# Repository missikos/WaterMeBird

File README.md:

# WaterMeBird

##Video Instructions
https://www.youtube.com/playlist?list=PLXV-vJmVgkyYVAK37a0ae-BBcncbxYWD5

#Advanced:

##PCB:
TBA

##Programming:
TBA

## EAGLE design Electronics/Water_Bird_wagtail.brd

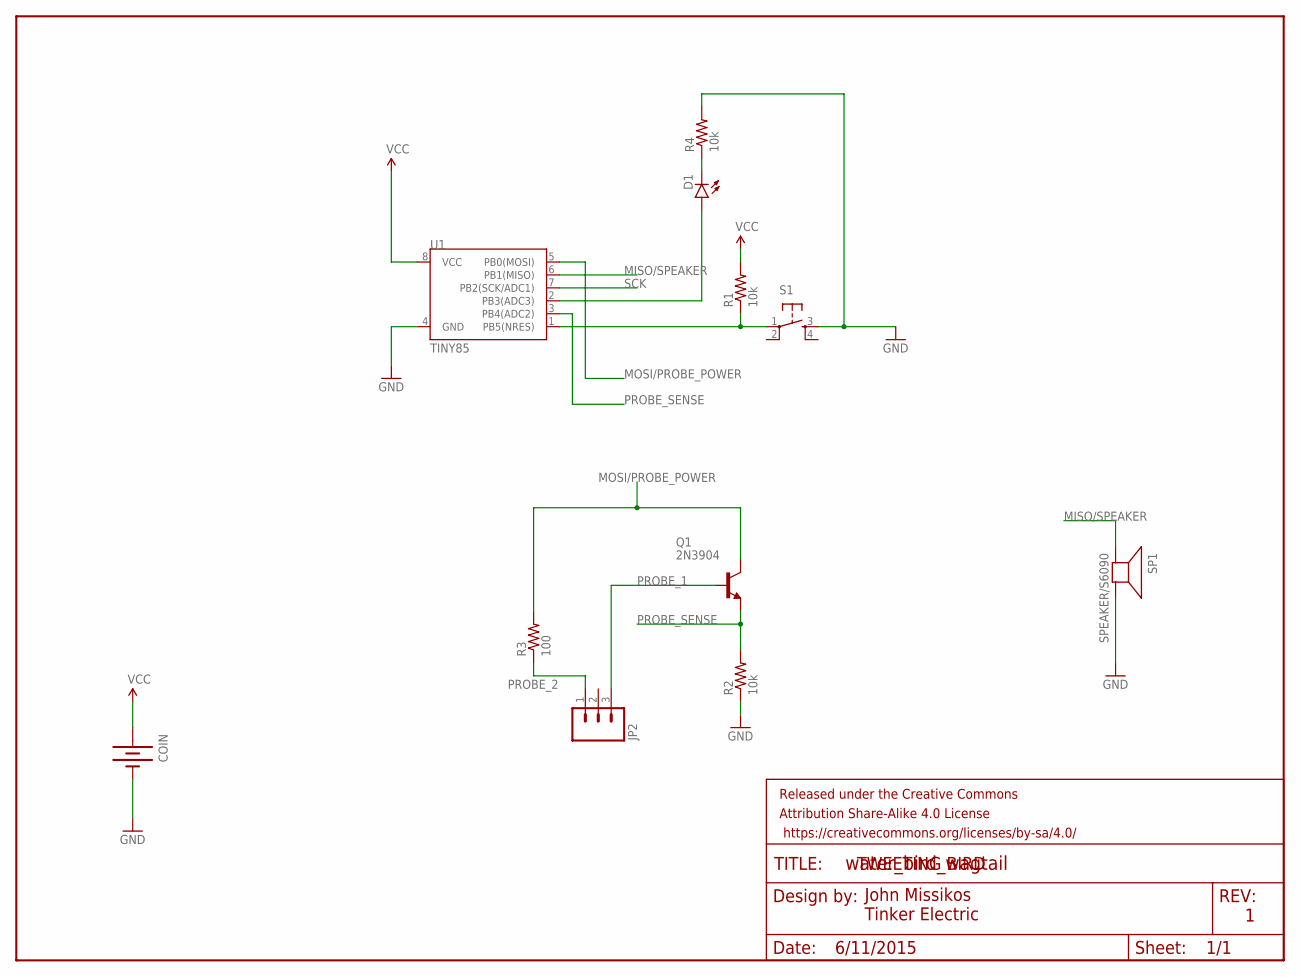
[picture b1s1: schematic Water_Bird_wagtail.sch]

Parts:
COIN: BATTERY_20MM20PTH; BATTCOM_20MM_PTH
D1: LED5MM
FRAME1: FRAME-LETTERNO_PACKAGE; DUMMY
JP2: M03-SCREW-5MM; SCREWTERMINAL-5MM-3
Q1: 2N3904; TO92-EBC-OVAL
R1, R2, R4: 10k; AXIAL-0.3
R3: 100; AXIAL-0.3
S1: TAC_SWITCHPTH; TACTILE-PTH
SP1: SPEAKER/S6090; S6090
U1: TINY85; DIP08

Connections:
GND: COIN.2 (-), R2.P$1 (1), R4.P$2 (2), S1.3, SP1.2 (-), U1.4 (GND)
MISO/SPEAKER: SP1.1 (+), U1.6 (PB1(MISO))
MOSI/PROBE_POWER: Q1.C, R3.P$2 (2), U1.5 (PB0(MOSI))
unnamed: D1.A, U1.2 (PB3(ADC3))
unnamed: D1.K (C), R4.P$1 (1)
PROBE_1: JP2.3, Q1.B
PROBE_2: JP2.1, R3.P$1 (1)
PROBE_SENSE: Q1.E, R2.P$2 (2), U1.3 (PB4(ADC2))
RESET: R1.P$1 (1), S1.1, U1.1 (PB5(NRES))
SCK: U1.7 (PB2(SCK/ADC1))
VCC: COIN.1 (+), R1.P$2 (2), U1.8 (VCC)

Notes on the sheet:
TWEETING BIRD
John Missikos Tinker Electric
6/11/2015

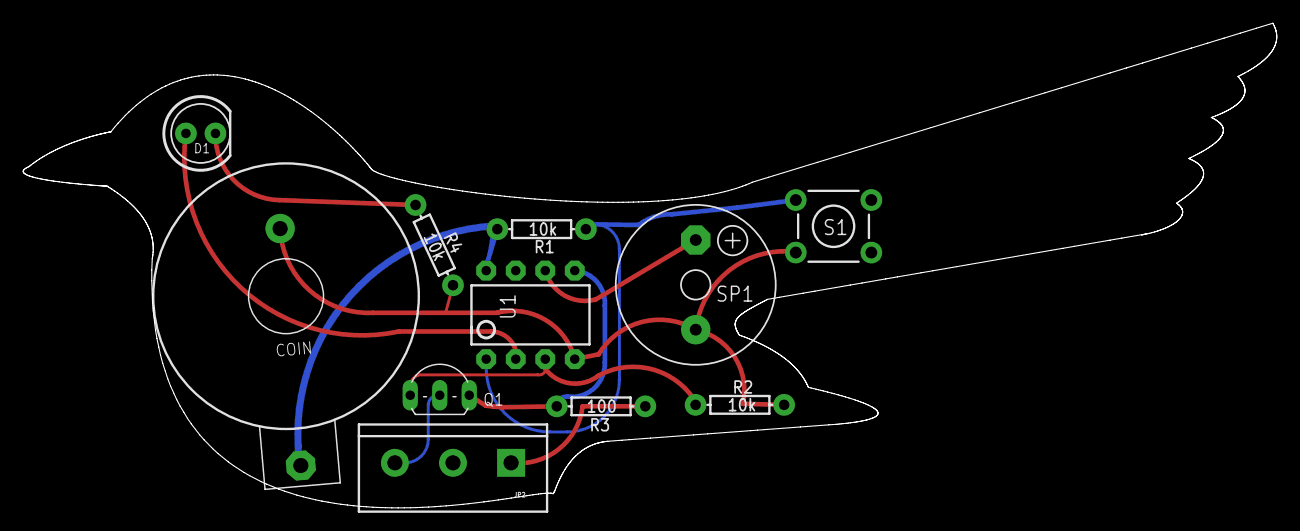
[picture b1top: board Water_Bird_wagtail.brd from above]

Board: 2 copper layers, 107.9 x 41.7 mm, 12 parts (0 on the bottom side), 10 nets.

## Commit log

2019-03-15 Initial and clean, this is V5.2
2021-06-04 docs
2022-03-29 Adding new version
2022-03-29 Added 'thick' version of footprints
2022-03-30 added outline and placed

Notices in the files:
Electronics/Water_Bird_wagtail.brd:
WaterBird v4 (c) 2016
parts and their libraries:
SparkFun-LED: Licensing: Creative Commons ShareAlike 4.0 International - https://creativecommons.org/licenses/by-sa/4.0
SparkFun-Aesthetics: Released under the Creative Commons Attribution Share-Alike 4.0 License
SparkFun-Aesthetics: https://creativecommons.org/licenses/by-sa/4.0
